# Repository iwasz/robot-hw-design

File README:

Open this repo with KiCad. Firmware is here : http://github.com/iwasz/robot-firmware

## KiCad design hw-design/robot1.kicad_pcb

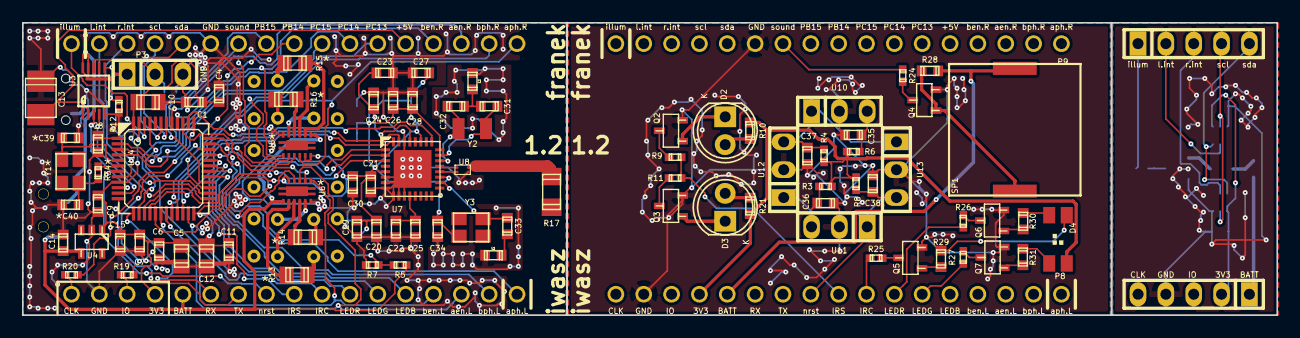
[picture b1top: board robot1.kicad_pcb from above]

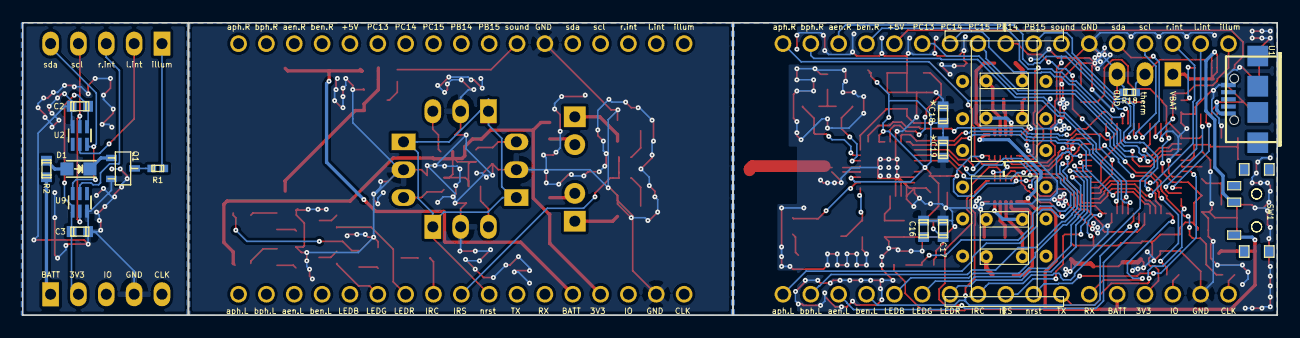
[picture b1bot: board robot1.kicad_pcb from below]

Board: 2 copper layers, 114.4 x 26.7 mm, 111 parts (17 on the bottom side), 114 nets.

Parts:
C1, C21, C27, C29: 1µF; c_0603
C2, C3, C6, C7, C8, C9, C11, C16, C17, C18, C19, C20, C25, C26, C28, C30, C35, C36, C37, C38: 100nF; c_0603
C4: 10nF; c_0603
C5, C10, C12: 4.7µF; c_0805
C13: 10µF; c_tant_B
C14, C15: 1µF X7R 10V; c_0603
C22, C23: 100pF; c_0603
C24: 150nF; c_0603
C31, C32: 22pF; c_0603
C33, C34, C39, C40: 15pF; c_0603
D1: LED; LED_0805
D2: VISHAY TLDR5800 (red 4°); LED-5MM
D3: OSRAM SFH4550 (IR 3°); LED-5MM
D4: Led_RGB_CA; PLCC4-LED
L1: INDUCTOR; c_0603
L2: 3.9 nH; c_0603
P1, P2, P8, P9: CONN_01X17; pin_socket_17
P3: CONN_01X03; pin_strip_3
P4: left_motor; stepper-small
P5: right_motor; stepper-small
P6, P7: CONN_01X05; pin_strip_5
Q1, Q2, Q3, Q4, Q5, Q6, Q7: BC847; sot23
R1, R5, R7, R9, R11, R24, R25, R26, R27: 1k; r_0402
R2: 80; r_0603
R3, R4, R6, R8: 1R; r_0402
R10: 130; r_0603
R12: 3k3; r_0402
R13, R14, R15, R16: R; r_0805
R17: AMCA31; r_1206
R18: 10k; r_0402
R19, R20: 22R; r_0402
R21: 180R; r_0603
R28: 1k; r_0603
R29: 200; r_0603
R30, R31: 30; r_0603
R34: 220; r_0402
SP1: SPEAKER; PKLCS-speaker
SW1: SWITCH_INV; 1437575-1
U1: usb-micro; conn_usb_B_micro_smd-2
U2, U9: TCS3472; SC70-6
U3: MCP73833; MSOP10
U4: MIC5501; sot23-5
U5, U6: drv8835
U7: BlueNRG; pvqfn-n32
U8: BALF-NRG-01D3
U10, U11, U12, U13: China-0038; pin_strip_3
U14: STM32F030CxTx; lqfp48
Y1, Y3: 16MHz; crystal_FA238-TSX3225
Y2: 32kHz; crystal_3.2_1.5

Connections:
+3.3VA: C2.2, C3.2, P6.2, U2.1, U9.1
+3.3VP: D4.1, P8.14, R3.1, R4.1, R6.1, R8.1, R10.2, R21.2
+3V3: C1.1, C4.1, C5.1, C6.1, C7.1, C8.1, C9.1, C10.1, C11.1, C12.1, C15.1, C16.2, C17.2, C18.2, C19.2, C20.1, C21.1, C26.2, C27.1, C28.1, C29.1, C30.1, P1.14, U4.1, U5.11, U5.12, U6.11, U6.12, U7.5, U7.19, U7.24, U7.27, U7.28, U14.1, U14.9, U14.24, U14.48
+5V: C13.1, P2.13, U1.1, U3.1, U3.2
+BATT: C14.1, P1.13, R5.2, SW1.1, U4.4, U5.1, U6.1
/bluetooth/ble_resetn: U7.25, U14.38
/bluetooth/ble_spi_clk: U7.2, U14.15
/bluetooth/ble_spi_cs: U7.31, U14.22
/bluetooth/ble_spi_irq: U7.3, U14.39
/bluetooth/ble_spi_miso: U7.32, U14.16
/bluetooth/ble_spi_mosi: U7.1, U14.17
/micro/aenbll: P1.3, U5.9, U14.18
/micro/aenblr: P2.15, U6.9, U14.41
/micro/aphasel: P1.1, U5.10, U14.35
/micro/aphaser: P2.17, U6.10, U14.20
/micro/benbll: P1.4, U5.7, U14.19
/micro/benblr: P2.14, U6.7, U14.40
/micro/bphasel: P1.2, U5.8, U14.36
/micro/bphaser: P2.16, U6.8, U14.21
/micro/complete: U3.4, U14.11
/micro/console_rx: P1.12, U14.13
/micro/console_tx: P1.11, U14.12
/micro/ir_cannon: P1.8, U14.45
/micro/ir_sense: P1.9, U14.32
/micro/led_b: P1.5, U14.29
/micro/led_g: P1.6, U14.30
/micro/led_r: P1.7, U14.31
/micro/nrst: P1.10, U14.7
/micro/pb14: P2.9, U14.27
/micro/pb15: P2.8, U14.28
/micro/pc13: P2.12, U14.2
/micro/pc14: P2.11, U14.3
/micro/pc15: P2.10, U14.4
/micro/photo_illumination: P2.1, U14.46
/micro/photo_l_int: P2.2, U14.25
/micro/photo_r_int: P2.3, U14.26
/micro/progress: U3.3, U14.10
/micro/scl: P2.4, U14.42
/micro/sda: P2.5, U14.43
/micro/sound: P2.7, U14.14
/micro/swdclk: R20.2, U14.37
/micro/swdio: R19.2, U14.34
/peripherals/ir_cannon: P8.9, R9.2, R11.2
/peripherals/ir_sense: P8.10, U10.1, U11.1, U12.1, U13.1
/peripherals/led_b: P8.6, R27.2
/peripherals/led_g: P8.7, R26.2
/peripherals/led_r: P8.8, R25.2
/peripherals/sound: P9.7, R24.2
/photo/photo_illumination: P7.1, R1.2
/photo/photo_l_int: P7.2, U2.5
/photo/photo_r_int: P7.3, U9.5
/photo/scl: P7.4, U2.2, U9.2
/photo/sda: P7.5, U2.6, U9.6
GND: C1.2, C4.2, C5.2, C6.2, C7.2, C8.2, C9.2, C10.2, C11.2, C12.2, C13.2, C14.2, C15.2, C16.1, C17.1, C18.1, C19.1, C20.2, C21.2, C22.2, C23.1, C24.1, C25.2, C26.1, C27.2, C28.2, C29.2, C30.2, C34.2, C39.2, C40.2, L1.2, L2.2, P1.16, P2.6, P3.3, R7.2, R12.2, R18.1, U1.5, U3.5, U4.2, U5.6, U6.6, U7.6, U7.7, U7.8, U7.9, U7.10, U7.11, U7.30, U7.33, U8.A2, U14.8, U14.23, U14.47
GNDA: C35.1, C36.1, C37.1, C38.1, P8.16, P9.6, Q2.3, Q3.3, Q4.3, Q5.3, Q6.3, Q7.3, U10.2, U11.2, U12.2, U13.2
GNDD: C2.1, C3.1, P6.4, Q1.3, U2.3, U9.3
unnamed: C22.1, C25.1, U7.12
unnamed: C23.2, C24.2, U7.29
unnamed: C31.1, U7.23, Y2.2
unnamed: C31.2, C32.2, L2.1
unnamed: C32.1, U7.22, Y2.1
unnamed: C33.1, U7.18, Y3.2
unnamed: C33.2, L1.1
unnamed: C34.1, U7.17, Y3.1
unnamed: C35.2, R6.2, U10.3
unnamed: C36.2, R3.2, U11.3
unnamed: C37.2, R4.2, U12.3
unnamed: C38.2, R8.2, U13.3
unnamed: C39.1, U14.5, Y1.1
unnamed: C40.1, R34.2, Y1.2
unnamed: D1.1, Q1.1
unnamed: D1.2, R2.1
unnamed: D2.1, Q2.1
unnamed: D2.2, R10.1
unnamed: D3.1, Q3.1
unnamed: D3.2, R21.1
unnamed: D4.2, R29.1
unnamed: D4.3, R30.1
unnamed: D4.4, R31.1
unnamed: P1.15, R19.1
unnamed: P1.17, R20.1
unnamed: P3.1, SW1.2, U3.9, U3.10
unnamed: P3.2, R18.2, U3.8
unnamed: P4.1, R13.2
unnamed: P4.2, U5.3
unnamed: P4.3, R14.2
unnamed: P4.4, U5.5
unnamed: P5.1, R15.2
unnamed: P5.2, U6.3
unnamed: P5.3, R16.2
unnamed: P5.4, U6.5
unnamed: Q1.2, R1.1
unnamed: Q2.2, R9.1
unnamed: Q3.2, R11.1
unnamed: Q4.1, R28.1, SP1.2
unnamed: Q4.2, R24.1
unnamed: Q5.1, R29.2
unnamed: Q5.2, R25.1
unnamed: Q6.1, R30.2
unnamed: Q6.2, R26.1
unnamed: Q7.1, R31.2
unnamed: Q7.2, R27.1
unnamed: R5.1, R7.1, U14.33
unnamed: R12.1, U3.6
unnamed: R13.1, U5.2
unnamed: R14.1, U5.4
unnamed: R15.1, U6.2
unnamed: R16.1, U6.4
unnamed: R17.2, U8.A1
unnamed: R34.1, U14.6
unnamed: U7.20, U8.B2
unnamed: U7.21, U8.B1
VAA: P8.13, R28.2, SP1.1
VCC: P6.1, R2.2

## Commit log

2016-05-01 Routing
2016-05-02 Routing complete?
2016-05-02 Groud planes improved
2016-05-02 Mounting holes for additional wheels or whatever
2016-05-03 patlabor logo
2016-05-05 Napisy, obrqazek
2016-06-20 Some changes in HW. Dunno.
2016-06-20 Firmware
2016-06-20 Gerbers
2016-06-20 Unused files removefd
2016-06-24 Motors spin
2016-07-06 Docs, PCB modified (problems with RF and low speed oscillator)
2016-07-07 Gerbery 1.1
2016-09-03 BT turned of/on #define
2016-09-03 Port na F030
2016-09-07 Serwis i charakterystyki dla robota,włączają się światełka
2016-09-08 First succesfull test, whre everything works. Lights, left and right motor are OK.
2016-09-08 control variables changed slightly to more intuitive
2016-09-14 version 1.1 works.
2016-10-24 3 boards split
2016-10-24 Changed to 2 boards layout. On the top one there is only : speaker, IR stuff, RGB led.
2016-10-25 Another idea of PCB split.
2016-10-25 2 boards and 1 little with color sensors.
2016-10-26 Hard work on the 1.2 PCB
2016-10-27 PCB 1.2 almost done, only shape could be improved.
2016-10-27 PCB shape improved
2016-10-27 Deleted some files
2016-10-30 gerbery wersja 1.2
2016-10-30 Deleted the firmware dir, its got its ow repository now.
2016-10-30 Moved all hw files to the main directory since firmware is removed from this repo to its own
2016-10-30 Added readme
